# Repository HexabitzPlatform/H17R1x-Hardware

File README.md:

# H17R1x-Hardware
Hexabitz 10A(RMS)/85V Stepper Drive Module Hardware Design

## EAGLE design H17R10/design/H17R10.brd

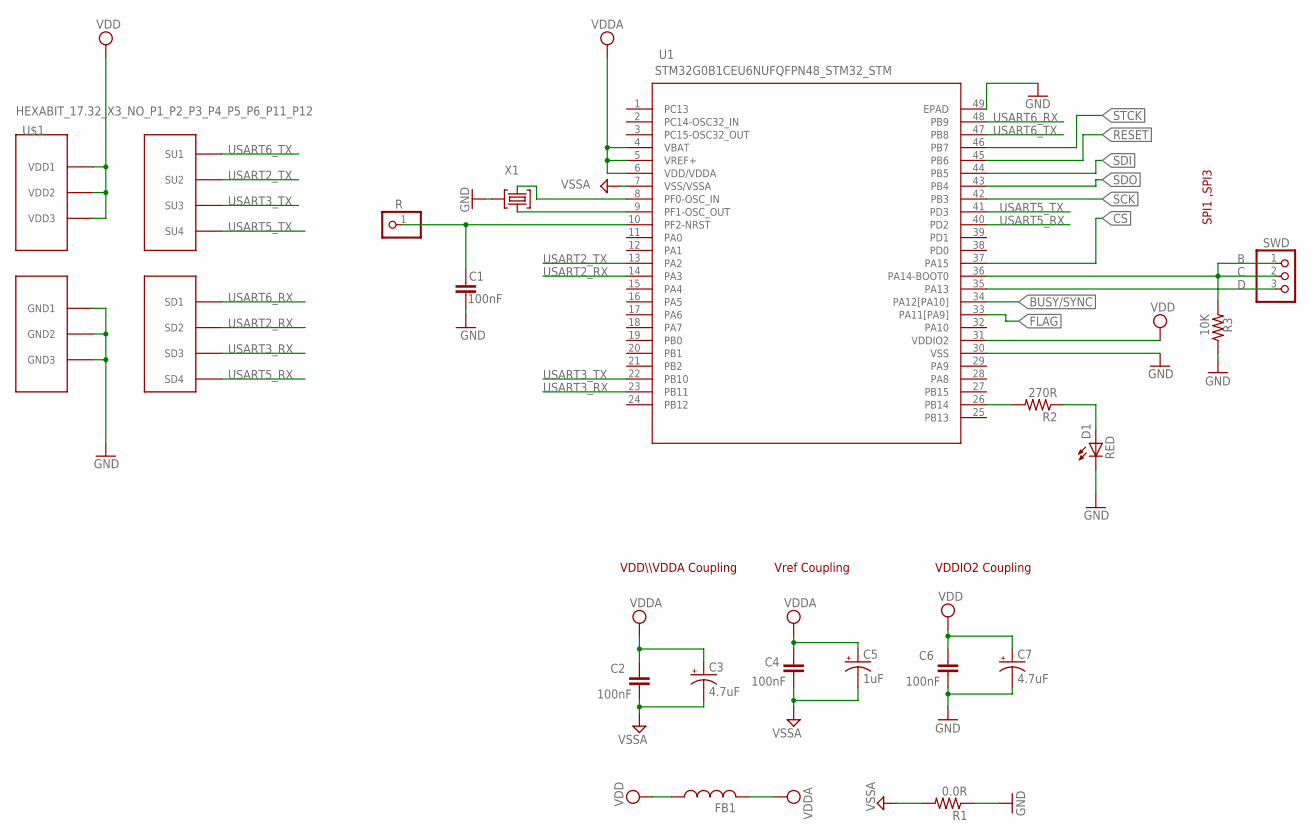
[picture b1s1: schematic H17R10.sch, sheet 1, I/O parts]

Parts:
C1: 100nF; C-0603; TOLERANCE 10%; VOLTAGE_RATING 16.0 V; MPN 0603YC104K4T2A
C2, C4, C6: 100nF; C-0603; TOLERANCE 10%; VOLTAGE_RATING 16.0 V; MPN '0603YC104K4T2A
C3: 4.7uF; C-0805-POL; TOLERANCE 20%; VOLTAGE_RATING 10.0 V; MPN '10TPU4R7MSI
C5: 1uF; C-0805-POL; TOLERANCE 20%; VOLTAGE_RATING 10.0 V; MPN 'CC0805KKX7R7BB105
C7: 4.7uF; C-0805-POL; TOLERANCE 10%; VOLTAGE_RATING 16.0 V; MPN '10TPU4R7MSI
D1: RED; VLMS1300-GS08
FB1: FB-TDK_MMZ1608Y300B; MPN MMZ1608Y300BTA00
R: PINHD-1X1; 1X01
R1: 0.0R; R-0603; MPN RC0603JR-070RL
R2: 270R; R-0603; MPN 'ERJ-3GEYJ271V
R3: 10K; R-0603; MPN '060300J0103T5E
SWD: PINHD-1X3; 1X03
U1: STM32G0B1CEU6NUFQFPN48_STM32_STM; HEXABITZ_ICS_UFQFPN48_STM32_STM
U$1: HEXABIT_17.32_X3_NO_P1_P2_P3_P4_P5_P6_P11_P12
X1: 8MHZ; XTALL_CSTCE8M00G52; MPN CSTNE8M00G550000R0

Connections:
BUSY/SYNC: U1.34 (PA12[PA10]); also elsewhere on the board
C: R3.2, SWD.1, SWD.2, U1.36 (PA14-BOOT0)
CS: U1.37 (PA15); also elsewhere on the board
D: SWD.3, U1.35 (PA13)
FLAG: U1.33 (PA11[PA9]); also elsewhere on the board
GND: C1.1, C6.1, C7.2 (-), D1.C, R1.1, R3.1, U1.30 (VSS), U1.49 (EPAD), U$1.PAD_PD12 (GND1), U$1.PAD_PD17 (GND2), U$1.PAD_PD19 (GND3), X1.P$2 (2)
unnamed: U1.8 (PF0-OSC_IN), X1.P$1 (1)
unnamed: U1.9 (PF1-OSC_OUT), X1.P$3 (3)
unnamed: C1.2, R.1, U1.10 (PF2-NRST)
unnamed: R2.2, U1.26 (PB14)
unnamed: D1.A, R2.1
RESET: U1.45 (PB6); also elsewhere on the board
SCK: U1.42 (PB3); also elsewhere on the board
SDI: U1.44 (PB5); also elsewhere on the board
SDO: U1.43 (PB4); also elsewhere on the board
STCK: U1.46 (PB7); also elsewhere on the board
USART2_RX: U1.14 (PA3), U$1.PAD_PD1 (SD2)
USART2_TX: U1.13 (PA2), U$1.PAD_PU1 (SU2)
USART3_RX: U1.23 (PB11), U$1.PAD_PD2 (SD3)
USART3_TX: U1.22 (PB10), U$1.PAD_PU2 (SU3)
USART5_RX: U1.40 (PD2), U$1.PAD_PD8 (SD4)
USART5_TX: U1.41 (PD3), U$1.PAD_PU8 (SU4)
USART6_RX: U1.48 (PB9), U$1.PAD_PD3 (SD1)
USART6_TX: U1.47 (PB8), U$1.PAD_PU3 (SU1)
VDD: C6.2, C7.1 (+), FB1.1, U1.31 (VDDIO2), U$1.PAD_PU12 (VDD1), U$1.PAD_PU17 (VDD2), U$1.PAD_PU19 (VDD3)
VDDA: C2.2, C3.1 (+), C4.2, C5.1 (+), FB1.2, U1.4 (VBAT), U1.5 (VREF+), U1.6 (VDD/VDDA); also elsewhere on the board
VSSA: C2.1, C3.2 (-), C4.1, C5.2 (-), R1.2, U1.7 (VSS/VSSA); also elsewhere on the board

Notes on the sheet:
VDDIO2 Coupling
VDD\\\VDDA Coupling
Vref Coupling
SPI1 ,SPI3

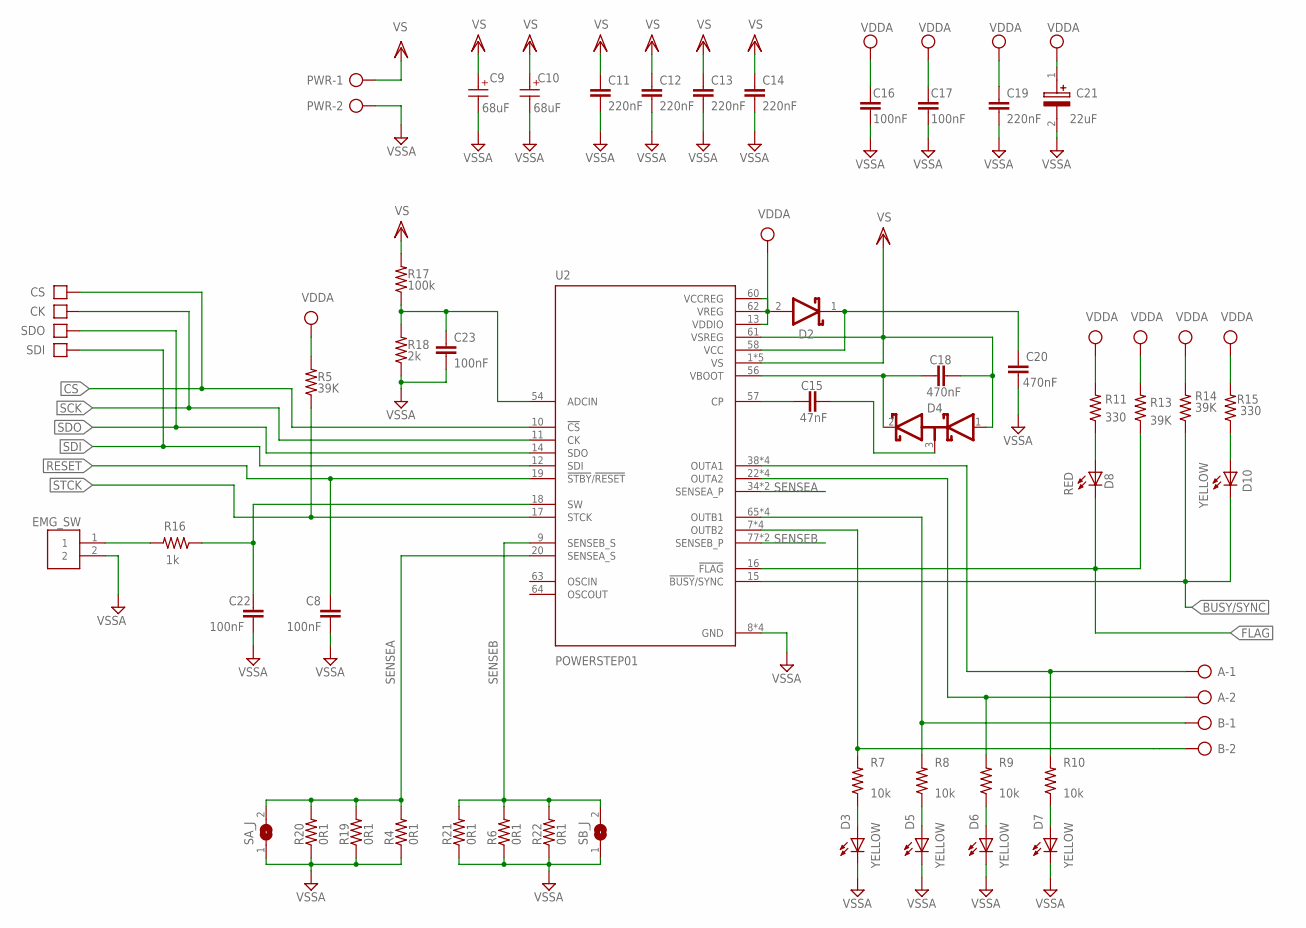
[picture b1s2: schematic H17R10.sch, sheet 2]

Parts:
A: AK500/2
B: AK500/2
C8, C22, C23: 100nF; C-0603; MPN C1608X7R1H104K080AA
C9, C10: 68uF; WCAP-ASLI_12.5X14(DXL)
C11, C12, C13, C14: 220nF; C-0805
C15: 47nF; C-0805; VOLTAGE_RATING 100V; MPN C0805C473K1RACTU
C16, C17: 100nF; C-0603; TOLERANCE 10%; VOLTAGE_RATING 16.0 V; MPN '0603YC104K4T2A
C18, C20: 470nF; C-0603; VOLTAGE_RATING 100V; MPN CGA3E3X7R1E474K080AE
C19: 220nF; C-0603; MPN CGA3E3X7R1V224K080AE
C21: 22uF; T491A
CK: PAD4
CS: PAD4
D2: STMICROELECTRONICS_BAT46ZFILMSTMICROELECTRONICS_B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; STMICROELECTRONICS_BAT46ZFILM_3
D3, D5, D6, D7, D10: YELLOW; VLMY1300-GS08; MPN LTST-C170YKT
D4: STMICROELECTRONICS_BAR43SFILMSTMICROELECTRONICS_B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; STMICROELECTRONICS_BAR43SFILM_0
D8: RED; VLMS1300-GS08; MPN LTST-C170-EKT
EMG_SW: 3-644456-2; TE_3-644456-2
PWR: AK500/2
R4, R6, R19, R20, R21, R22: 0R1; R2512; MPN PE2512FKE7W0R1L
R5, R13, R14: 39K; R-0603; MPN RC0603FR-0739KL
R7, R8, R9, R10: 10k; R-0805; MPN ERJ-6GEYJ103V
R11, R15: 330; R-0603; MPN RC0603JR-07330RL
R16: 1k; R-0603; MPN RC0603JR-07330RL
R17: 100k; R-0603; MPN RC0603FR-0739KL
R18: 2k; R-0603; MPN RC0603FR-0739KL
SA_J: SJW
SB_J: SJW
SDI: PAD4
SDO: PAD4
U2: POWERSTEP01; IC_POWERSTEP01

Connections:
BUSY/SYNC: D10.C, R14.1, U2.15 (!BUSY!/SYNC); also elsewhere on the board
CS: CS.P$1, U2.10 (!CS); also elsewhere on the board
FLAG: D8.C, R13.1, U2.16 (!FLAG); also elsewhere on the board
unnamed: C22.1, R16.1, U2.18 (SW)
unnamed: C15.1, U2.57 (CP)
unnamed: D10.A, R15.1
unnamed: D7.A, R10.1
unnamed: C23.1, R17.1, R18.2, U2.54 (ADCIN)
unnamed: D3.A, R7.1
unnamed: D8.A, R11.1
unnamed: D5.A, R8.1
unnamed: D6.A, R9.1
unnamed: C18.2, D4.2 (K1), U2.56 (VBOOT)
unnamed: C20.1, D2.1 (CATHODE), U2.58 (VCC)
unnamed: C15.2, D4.3 (A1/K2)
OUTA1: A.2, R10.2, U2.38 (OUTA1), U2.42 (OUTA1), U2.53 (OUTA1), U2.EPAD4 (OUTA1)
OUTA2: A.1, R9.2, U2.22 (OUTA2), U2.33 (OUTA2), U2.37 (OUTA2), U2.EPAD3 (OUTA2)
OUTB1: B.1, R8.2, U2.65 (OUTB1), U2.76 (OUTB1), U2.80 (OUTB1), U2.EPAD7 (OUTB1)
OUTB2: B.2, R7.2, U2.7 (OUTB2), U2.81 (OUTB2), U2.85 (OUTB2), U2.EPAD8 (OUTB2)
RESET: C8.1, U2.19 (!STBY!/!RESET); also elsewhere on the board
SCK: CK.P$1, U2.11 (CK); also elsewhere on the board
SDI: SDI.P$1, U2.12 (SDI); also elsewhere on the board
SDO: SDO.P$1, U2.14 (SDO); also elsewhere on the board
SENSEA: R4.2, R19.2, R20.2, SA_J.2, U2.20 (SENSEA_S), U2.34 (SENSEA_P), U2.39 (SENSEA_P)
SENSEB: R6.2, R21.2, R22.2, SB_J.2, U2.9 (SENSEB_S), U2.77 (SENSEB_P), U2.82 (SENSEB_P)
STCK: R5.1, U2.17 (STCK); also elsewhere on the board
SW: EMG_SW.1, R16.2
VDDA: C16.2, C17.2, C19.1, C21.1 (+), D2.2 (ANODE), R5.2, R11.2, R13.2, R14.2, R15.2, U2.13 (VDDIO), U2.60 (VCCREG), U2.62 (VREG); also elsewhere on the board
VS: C9.1 (+), C10.1 (+), C11.1, C12.1, C13.1, C14.1, C18.1, D4.1 (A2), PWR.1, R17.2, U2.1 (VS), U2.23 (VS), U2.43 (VS), U2.55 (VS), U2.61 (VSREG), U2.66 (VS)
VSSA: C8.2, C9.2 (-), C10.2 (-), C11.2, C12.2, C13.2, C14.2, C16.1, C17.1, C19.2, C20.2, C21.2 (-), C22.2, C23.2, D3.C, D5.C, D6.C, D7.C, EMG_SW.2, PWR.2, R4.1, R6.1, R18.1, R19.1, R20.1, R21.1, R22.1, SA_J.1, SB_J.1, U2.8 (GND), U2.21 (GND), U2.59 (GND), U2.EPAD9 (GND); also elsewhere on the board

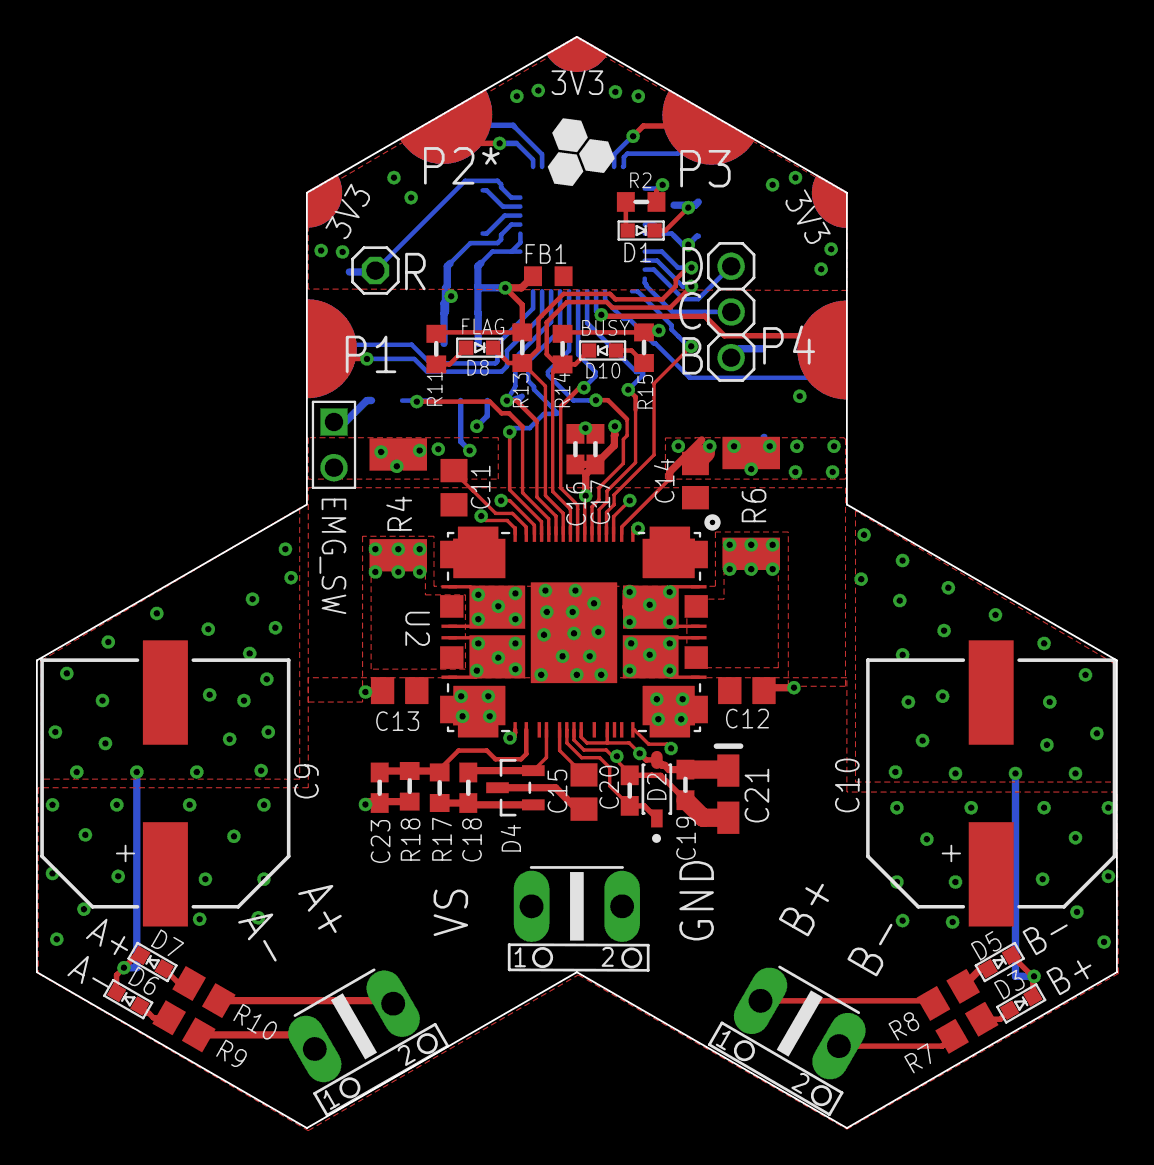
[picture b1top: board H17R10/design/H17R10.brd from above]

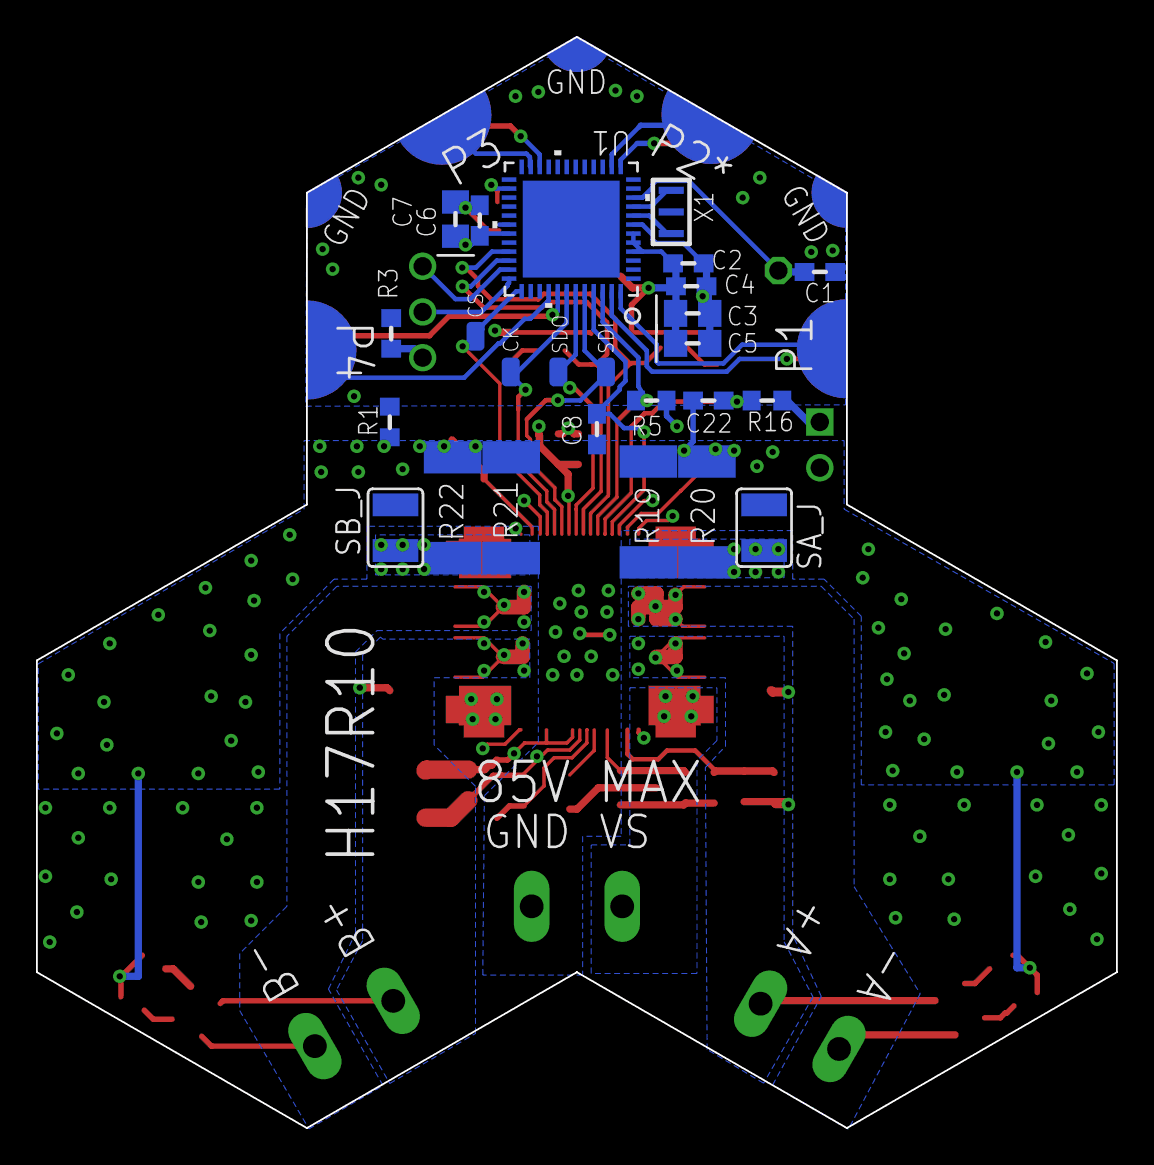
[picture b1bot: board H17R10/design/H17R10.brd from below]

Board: 4 copper layers, 60.0 x 60.6 mm, 70 parts (25 on the bottom side), 47 nets.

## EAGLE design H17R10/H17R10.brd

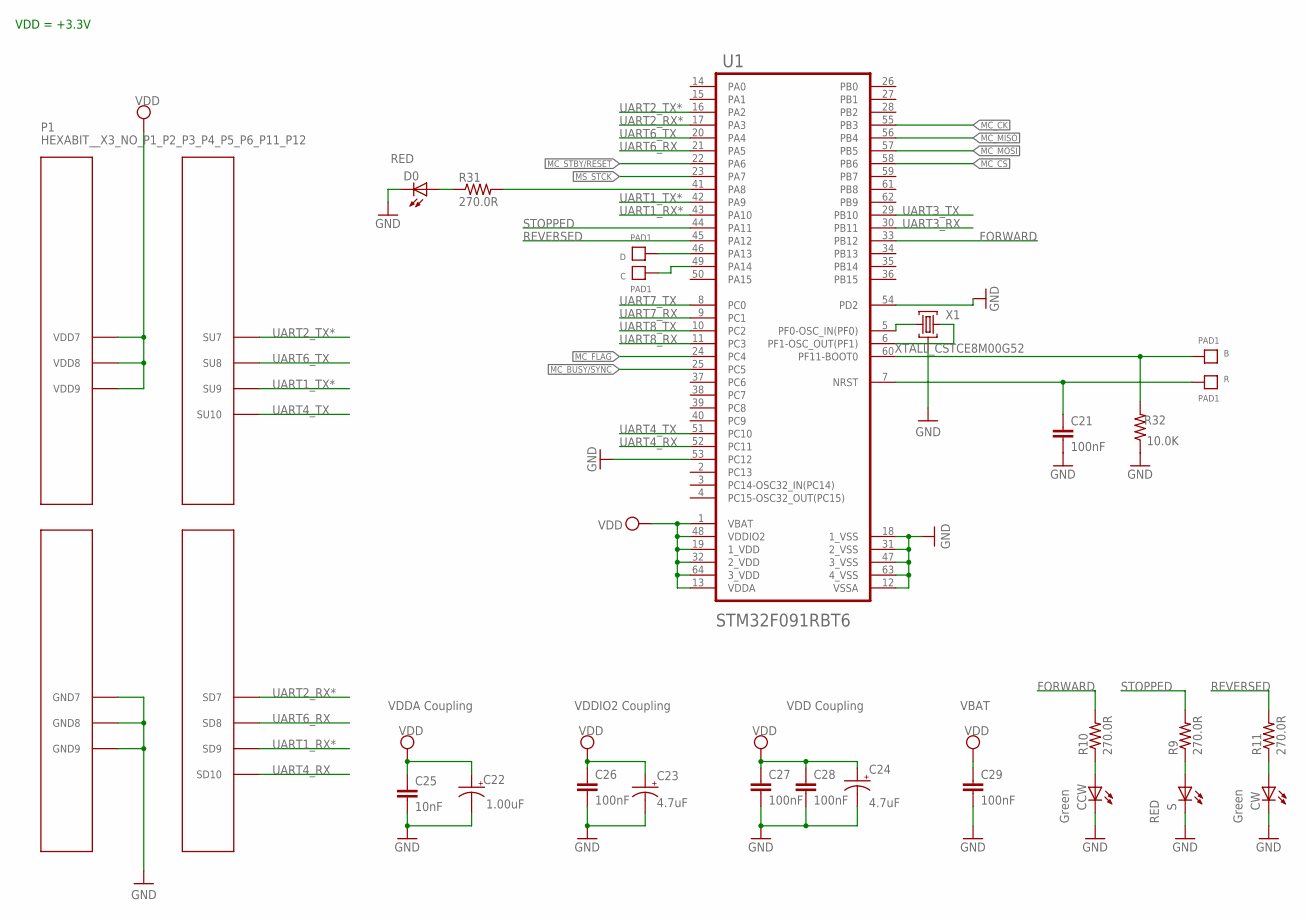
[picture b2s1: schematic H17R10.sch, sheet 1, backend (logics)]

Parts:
B: PAD1
C: PAD1
C21, C26, C28: 100nF; C-0603; TOLERANCE 10%; VOLTAGE_RATING 10V; MPN C0603C104K8RACTU
C22: 1.00uF; C-0805-POL; TOLERANCE 10%; VOLTAGE_RATING 16V; MPN CC0805KKX7R7BB105
C23, C24: 4.7uF; C-0805-POL; TOLERANCE 10%; VOLTAGE_RATING 25V; MPN GRM21BC81E475KA12L
C25: 10nF; C-0603; TOLERANCE 10%; VOLTAGE_RATING 50V; MPN C0603C103K5RACTU
C27: 100nF; C-0603; TOLERANCE 10%; VOLTAGE_RATING 10; MPN C0603C104K8RACTU
C29: 100nF; C-0603; TOLERANCE 10V; VOLTAGE_RATING 10%; MPN C0603C104K8RACTU
CCW: Green; VLMTG1300-GS08; MPN VLMS1300-GS08
CW: Green; VLMTG1300-GS08; MPN VLMS1300-GS08
D: PAD1
D0: RED; VLMS1300-GS08; MPN VLMS1300-GS08
P1: HEXABIT__X3_NO_P1_P2_P3_P4_P5_P6_P11_P12; HEXABIT_17.32_X3_NO_P1_P2_P3_P4_P5_P6_P11_P12
R: PAD1
R9, R10, R11, R31: 270.0R; R-0603; TOLERANCE 1%; MPN RC0603FR-07270RL
R32: 10.0K; R-0603; TOLERANCE 5%; MPN RC0603JR-0710KL
S: RED; VLMS1300-GS08; MPN VLMS1300-GS08
U1: STM32F091RBT6STMICROELECTRONICS_STM32F091RBT6_0_1; STMICROELECTRONICS_STM32F091RBT6_1
X1: XTALL_CSTCE8M00G52

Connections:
B1: B.P$1, B.P$2, R32.2, U1.60 (PF11-BOOT0)
FORWARD: R10.2, U1.33 (PB12)
GND: C21.2, C22.2 (-), C23.2 (-), C24.2 (-), C25.2, C26.2, C27.2, C28.2, C29.2, CCW.C, CW.C, D0.C, P1.PAD_PD12 (GND7), P1.PAD_PD17 (GND8), P1.PAD_PD19 (GND9), R32.1, S.C, U1.12 (VSSA), U1.18 (1_VSS), U1.31 (2_VSS), U1.47 (3_VSS), U1.53 (PC12), U1.54 (PD2), U1.63 (4_VSS), X1.P$2 (2); also elsewhere on the board
MC_BUSY/SYNC: U1.25 (PC5); also elsewhere on the board
MC_CK: U1.55 (PB3); also elsewhere on the board
MC_CS: U1.58 (PB6); also elsewhere on the board
MC_FLAG: U1.24 (PC4); also elsewhere on the board
MC_MISO: U1.56 (PB4); also elsewhere on the board
MC_MOSI: U1.57 (PB5); also elsewhere on the board
MC_STBY/RESET: U1.22 (PA6); also elsewhere on the board
MS_STCK: U1.23 (PA7); also elsewhere on the board
unnamed: R31.2, U1.41 (PA8)
unnamed: D0.A, R31.1
unnamed: U1.5 (PF0-OSC_IN(PF0)), X1.P$1 (1)
unnamed: U1.6 (PF1-OSC_OUT(PF1)), X1.P$3 (3)
unnamed: D.P$1, D.P$2, U1.46 (PA13)
unnamed: C.P$1, C.P$2, U1.49 (PA14)
unnamed: R9.1, S.A
unnamed: CCW.A, R10.1
unnamed: CW.A, R11.1
R1: C21.1, R.P$1, R.P$2, U1.7 (NRST)
REVERSED: R11.2, U1.45 (PA12)
STOPPED: R9.2, U1.44 (PA11)
UART1_RX*: P1.PAD_PD2 (SD9), U1.43 (PA10)
UART1_TX*: P1.PAD_PU2 (SU9), U1.42 (PA9)
UART2_RX*: P1.PAD_PD3 (SD7), U1.17 (PA3)
UART2_TX*: P1.PAD_PU3 (SU7), U1.16 (PA2)
UART3_RX: U1.30 (PB11)
UART3_TX: U1.29 (PB10)
UART4_RX: P1.PAD_PD8 (SD10), U1.52 (PC11)
UART4_TX: P1.PAD_PU8 (SU10), U1.51 (PC10)
UART6_RX: P1.PAD_PD1 (SD8), U1.21 (PA5)
UART6_TX: P1.PAD_PU1 (SU8), U1.20 (PA4)
UART7_RX: U1.9 (PC1)
UART7_TX: U1.8 (PC0)
UART8_RX: U1.11 (PC3)
UART8_TX: U1.10 (PC2)
VDD: C22.1 (+), C23.1 (+), C24.1 (+), C25.1, C26.1, C27.1, C28.1, C29.1, P1.PAD_PU12 (VDD7), P1.PAD_PU17 (VDD8), P1.PAD_PU19 (VDD9), U1.1 (VBAT), U1.13 (VDDA), U1.19 (1_VDD), U1.32 (2_VDD), U1.48 (VDDIO2), U1.64 (3_VDD); also elsewhere on the board

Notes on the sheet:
VDDA Coupling
VDDIO2 Coupling
VDD Coupling
VBAT
VDD = +3.3V

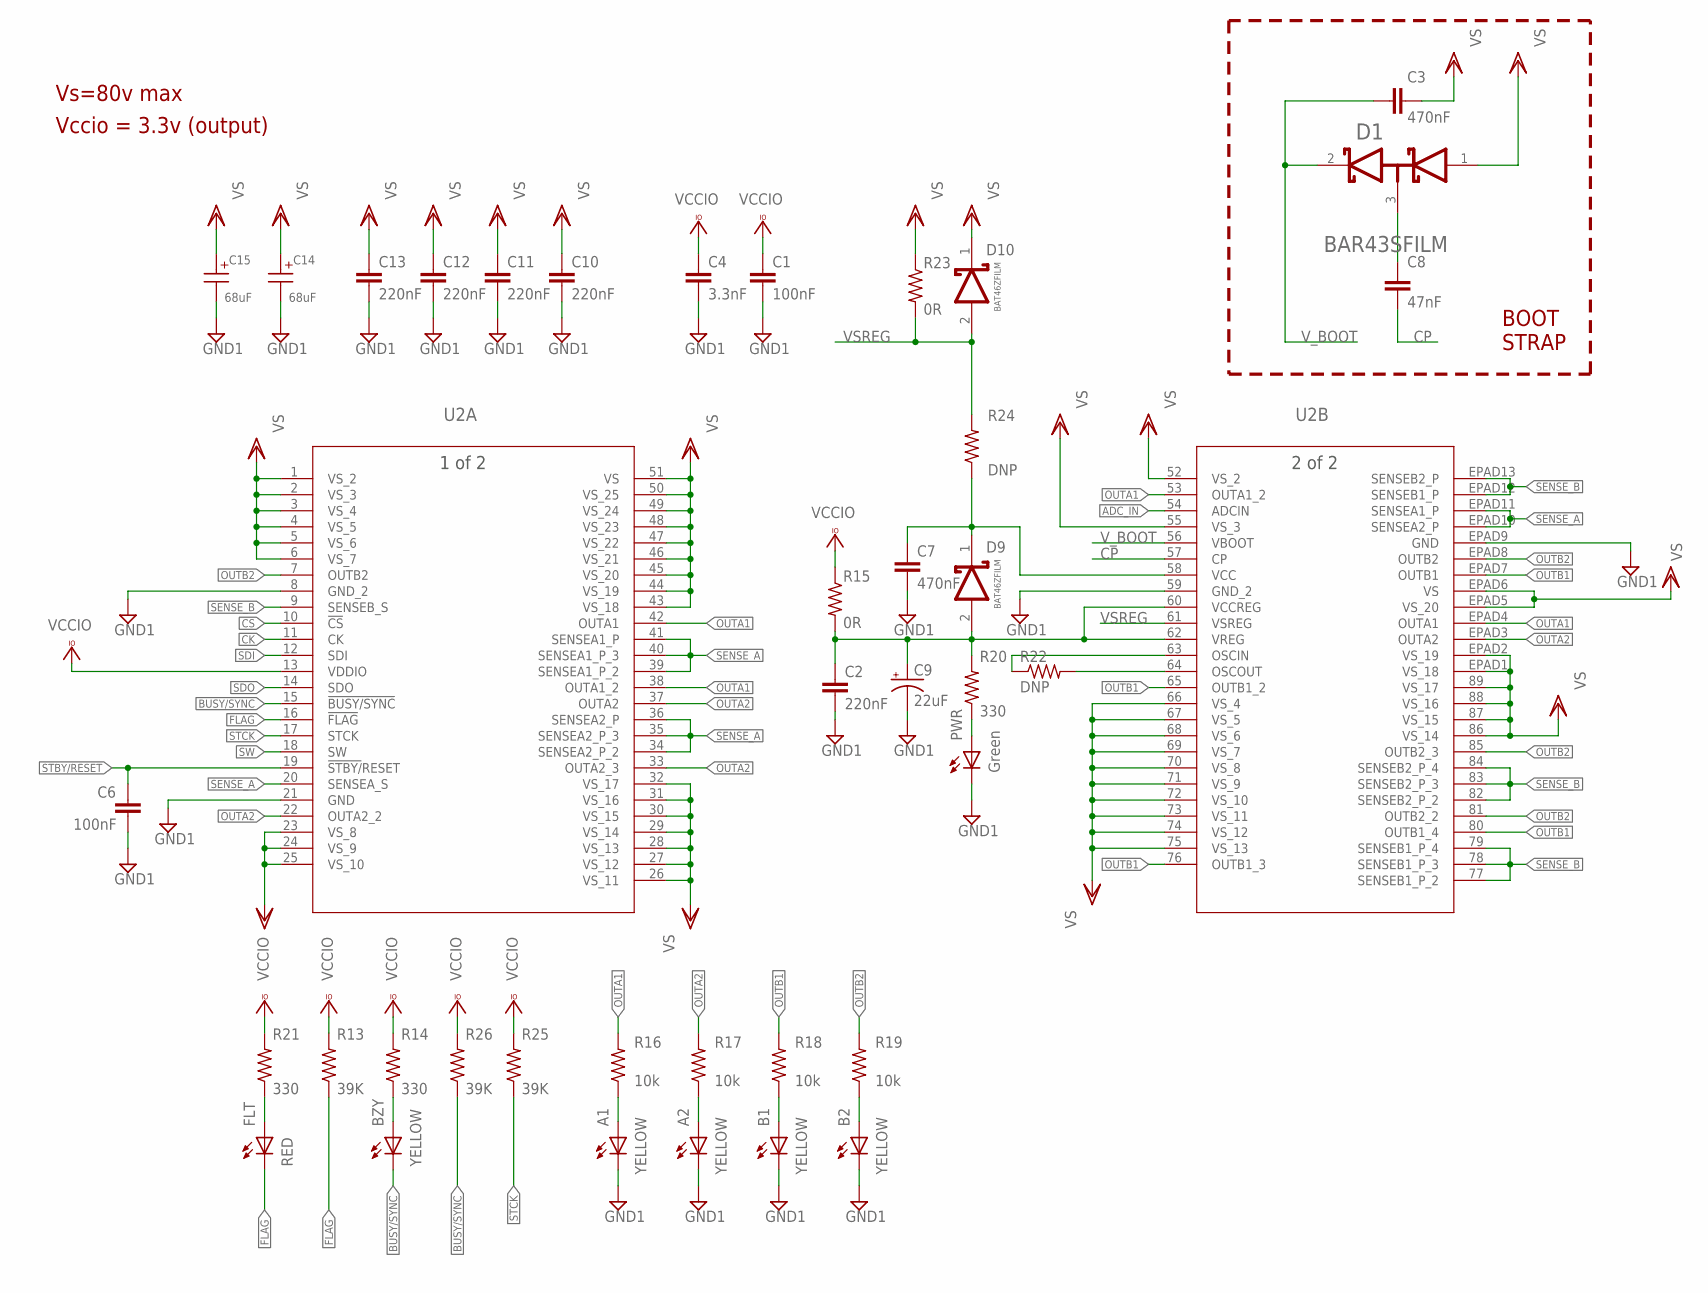
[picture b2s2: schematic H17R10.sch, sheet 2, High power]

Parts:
A1, A2: YELLOW; VLMY1300-GS08; MPN LTST-C170YKT
B1, B2: YELLOW; VLMY1300-GS08; MPN LTST-C170YKT
BZY: YELLOW; VLMY1300-GS08; MPN LTST-C170YKT
C1, C6: 100nF; C-0603; MPN C1608X7R1H104K080AA
C2: 220nF; C-0603; MPN CGA3E3X7R1V224K080AE
C3, C7: 470nF; C-0603; MPN CGA3E3X7R1E474K080AE
C4: 3.3nF; C-0603; MPN C1608X7R1H104K080AA
C8: 47nF; C-0805; VOLTAGE_RATING 100V; MPN C0805C473K1RACTU
C9: 22uF; C-0805-POL; VOLTAGE_RATING 6.3V; MPN T491A226K006AT
C10, C11, C12, C13: 220nF; C-0805
C14, C15: 68uF; WCAP-ASLI_12.5X14(DXL)
D1: STMICROELECTRONICS_BAR43SFILMSTMICROELECTRONICS_B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; STMICROELECTRONICS_BAR43SFILM_0
D9, D10: STMICROELECTRONICS_BAT46ZFILMSTMICROELECTRONICS_B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; STMICROELECTRONICS_BAT46ZFILM_3
FLT: RED; VLMS1300-GS08; MPN LTST-C170-EKT
PWR: Green; VLMTG1300-GS08; MPN LTST-C170GKT
R13, R25, R26: 39K; R-0603; MPN RC0603FR-0739KL
R14, R20, R21: 330; R-0603; MPN RC0603JR-07330RL
R15, R23: 0R; R-0603; MPN RC0603JR-070RL
R16, R17, R18, R19: 10k; R-0805; MPN ERJ-6GEYJ103V
R22: DNP; R-0603; MPN DNP
R24: DNP; R-0805
U2: POWERSTEP01; VFQFPN89_11X14X1_STM

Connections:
ADC_IN: U2.54 (ADCIN); also elsewhere on the board
BUSY/SYNC: BZY.C, R26.1, U2.15 (!BUSY/SYNC); also elsewhere on the board
CK: U2.11 (CK); also elsewhere on the board
CP: C8.1, U2.57 (CP)
CS: U2.10 (!CS); also elsewhere on the board
FLAG: FLT.C, R13.1, U2.16 (!FLAG); also elsewhere on the board
GND1: A1.C, A2.C, B1.C, B2.C, C1.2, C2.2, C4.2, C6.2, C7.2, C9.2 (-), C10.2, C11.2, C12.2, C13.2, C14.2 (-), C15.2 (-), PWR.C, U2.8 (GND_2), U2.21 (GND), U2.59 (GND_2), U2.EPAD9 (GND); also elsewhere on the board
unnamed: C2.1, C9.1 (+), D9.2 (ANODE), R15.2, R20.2, U2.60 (VCCREG), U2.62 (VREG)
unnamed: C8.2, D1.3 (A1/K2)
unnamed: C7.1, D9.1 (CATHODE), R24.1, U2.58 (VCC)
unnamed: A1.A, R16.1
unnamed: BZY.A, R14.1
unnamed: FLT.A, R21.1
unnamed: PWR.A, R20.1
unnamed: A2.A, R17.1
unnamed: B1.A, R18.1
unnamed: B2.A, R19.1
unnamed: R22.2, U2.64 (OSCOUT)
unnamed: R22.1, U2.63 (OSCIN)
OUTA1: R16.2, U2.38 (OUTA1_2), U2.42 (OUTA1), U2.53 (OUTA1_2), U2.EPAD4 (OUTA1); also elsewhere on the board
OUTA2: R17.2, U2.22 (OUTA2_2), U2.33 (OUTA2_3), U2.37 (OUTA2), U2.EPAD3 (OUTA2); also elsewhere on the board
OUTB1: R18.2, U2.65 (OUTB1_2), U2.76 (OUTB1_3), U2.80 (OUTB1_4), U2.EPAD7 (OUTB1); also elsewhere on the board
OUTB2: R19.2, U2.7 (OUTB2), U2.81 (OUTB2_2), U2.85 (OUTB2_3), U2.EPAD8 (OUTB2); also elsewhere on the board
SDI: U2.12 (SDI); also elsewhere on the board
SDO: U2.14 (SDO); also elsewhere on the board
SENSE_A: U2.20 (SENSEA_S), U2.34 (SENSEA2_P_2), U2.35 (SENSEA2_P_3), U2.36 (SENSEA2_P), U2.39 (SENSEA1_P_2), U2.40 (SENSEA1_P_3), U2.41 (SENSEA1_P), U2.EPAD10 (SENSEA2_P), U2.EPAD11 (SENSEA1_P); also elsewhere on the board
SENSE_B: U2.9 (SENSEB_S), U2.77 (SENSEB1_P_2), U2.78 (SENSEB1_P_3), U2.79 (SENSEB1_P_4), U2.82 (SENSEB2_P_2), U2.83 (SENSEB2_P_3), U2.84 (SENSEB2_P_4), U2.EPAD12 (SENSEB1_P), U2.EPAD13 (SENSEB2_P); also elsewhere on the board
STBY/RESET: C6.1, U2.19 (!STBY/!RESET); also elsewhere on the board
STCK: R25.1, U2.17 (STCK); also elsewhere on the board
SW: U2.18 (SW); also elsewhere on the board
VCCIO: C1.1, C4.1, R13.2, R14.2, R15.1, R21.2, R25.2, R26.2, U2.13 (VDDIO); also elsewhere on the board
VSREG: D10.2 (ANODE), R23.2, R24.2, U2.61 (VSREG)
VSS: C3.2, C10.1, C11.1, C12.1, C13.1, C14.1 (+), C15.1 (+), D1.1 (A2), D10.1 (CATHODE), R23.1, U2.1 (VS_2), U2.2 (VS_3), U2.3 (VS_4), U2.4 (VS_5), U2.5 (VS_6), U2.6 (VS_7), U2.23 (VS_8), U2.24 (VS_9), U2.25 (VS_10), U2.26 (VS_11), U2.27 (VS_12), U2.28 (VS_13), U2.29 (VS_14), U2.30 (VS_15), U2.31 (VS_16), U2.32 (VS_17), U2.43 (VS_18), U2.44 (VS_19), U2.45 (VS_20), U2.46 (VS_21), U2.47 (VS_22), U2.48 (VS_23), U2.49 (VS_24), U2.50 (VS_25), U2.51 (VS), U2.52 (VS_2), U2.55 (VS_3), U2.66 (VS_4), U2.67 (VS_5), U2.68 (VS_6), U2.69 (VS_7), U2.70 (VS_8), U2.71 (VS_9), U2.72 (VS_10), U2.73 (VS_11), U2.74 (VS_12), U2.75 (VS_13), U2.86 (VS_14), U2.87 (VS_15), U2.88 (VS_16), U2.89 (VS_17), U2.EPAD1 (VS_18), U2.EPAD2 (VS_19), U2.EPAD5 (VS_20), U2.EPAD6 (VS); also elsewhere on the board
V_BOOT: C3.1, D1.2 (K1), U2.56 (VBOOT)

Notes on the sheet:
BOOT STRAP
Vs=80v max
Vccio = 3.3v (output)

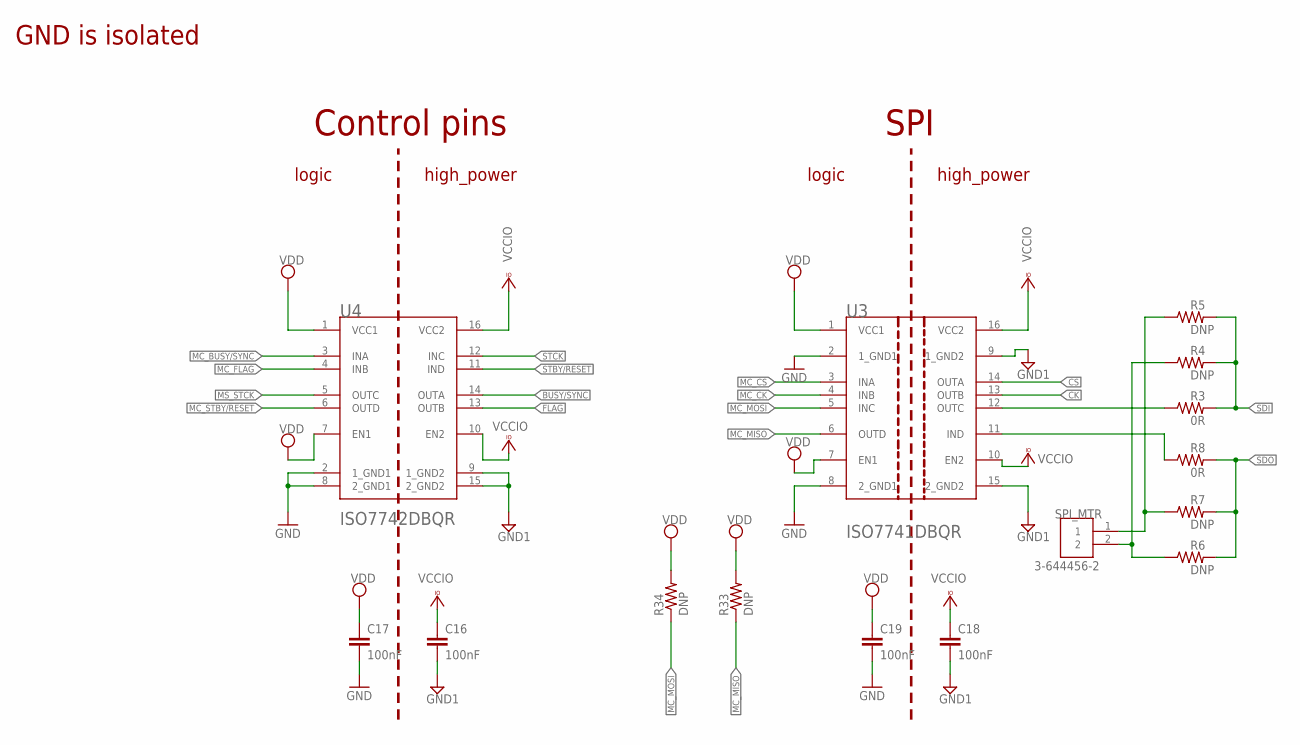
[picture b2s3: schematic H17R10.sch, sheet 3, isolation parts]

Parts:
C16, C17, C18, C19: 100nF; C-0603; MPN C1608X7R1H104K080AA
R3, R8: 0R; R-0603; MPN RC0603JR-070RL
R4, R5, R6, R7: DNP; R-0603; MPN DNP
R33, R34: DNP; R-0603
SPI_MTR: 3-644456-2; TE_3-644456-2
U3: TEXAS_INSTRUMENTS_ISO7741DBQRTEXAS_INSTRUMENTS_IS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; TEXAS_INSTRUMENTS_ISO7741DBQR_0
U4: TEXAS_INSTRUMENTS_ISO7742DBQRTEXAS_INSTRUMENTS_IS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; TEXAS_INSTRUMENTS_ISO7742DBQR_3

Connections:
BUSY/SYNC: U4.14 (OUTA); also elsewhere on the board
CK: U3.13 (OUTB); also elsewhere on the board
CS: U3.14 (OUTA); also elsewhere on the board
FLAG: U4.13 (OUTB); also elsewhere on the board
GND: C17.2, C19.2, U3.2 (1_GND1), U3.8 (2_GND1), U4.2 (1_GND1), U4.8 (2_GND1); also elsewhere on the board
GND1: C16.2, C18.2, U3.9 (1_GND2), U3.15 (2_GND2), U4.9 (1_GND2), U4.15 (2_GND2); also elsewhere on the board
MC_BUSY/SYNC: U4.3 (INA); also elsewhere on the board
MC_CK: U3.4 (INB); also elsewhere on the board
MC_CS: U3.3 (INA); also elsewhere on the board
MC_FLAG: U4.4 (INB); also elsewhere on the board
MC_MISO: R33.1, U3.6 (OUTD); also elsewhere on the board
MC_MOSI: R34.1, U3.5 (INC); also elsewhere on the board
MC_STBY/RESET: U4.6 (OUTD); also elsewhere on the board
MS_STCK: U4.5 (OUTC); also elsewhere on the board
unnamed: R3.1, U3.12 (OUTC)
unnamed: R8.1, U3.11 (IND)
unnamed: R4.1, R6.1, SPI_MTR.2
unnamed: R5.1, R7.1, SPI_MTR.1
SDI: R3.2, R4.2, R5.2; also elsewhere on the board
SDO: R6.2, R7.2, R8.2; also elsewhere on the board
STBY/RESET: U4.11 (IND); also elsewhere on the board
STCK: U4.12 (INC); also elsewhere on the board
VCCIO: C16.1, C18.1, U3.10 (EN2), U3.16 (VCC2), U4.10 (EN2), U4.16 (VCC2); also elsewhere on the board
VDD: C17.1, C19.1, R33.2, R34.2, U3.1 (VCC1), U3.7 (EN1), U4.1 (VCC1), U4.7 (EN1); also elsewhere on the board

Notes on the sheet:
GND is isolated
high_power
logic
SPI
Control pins

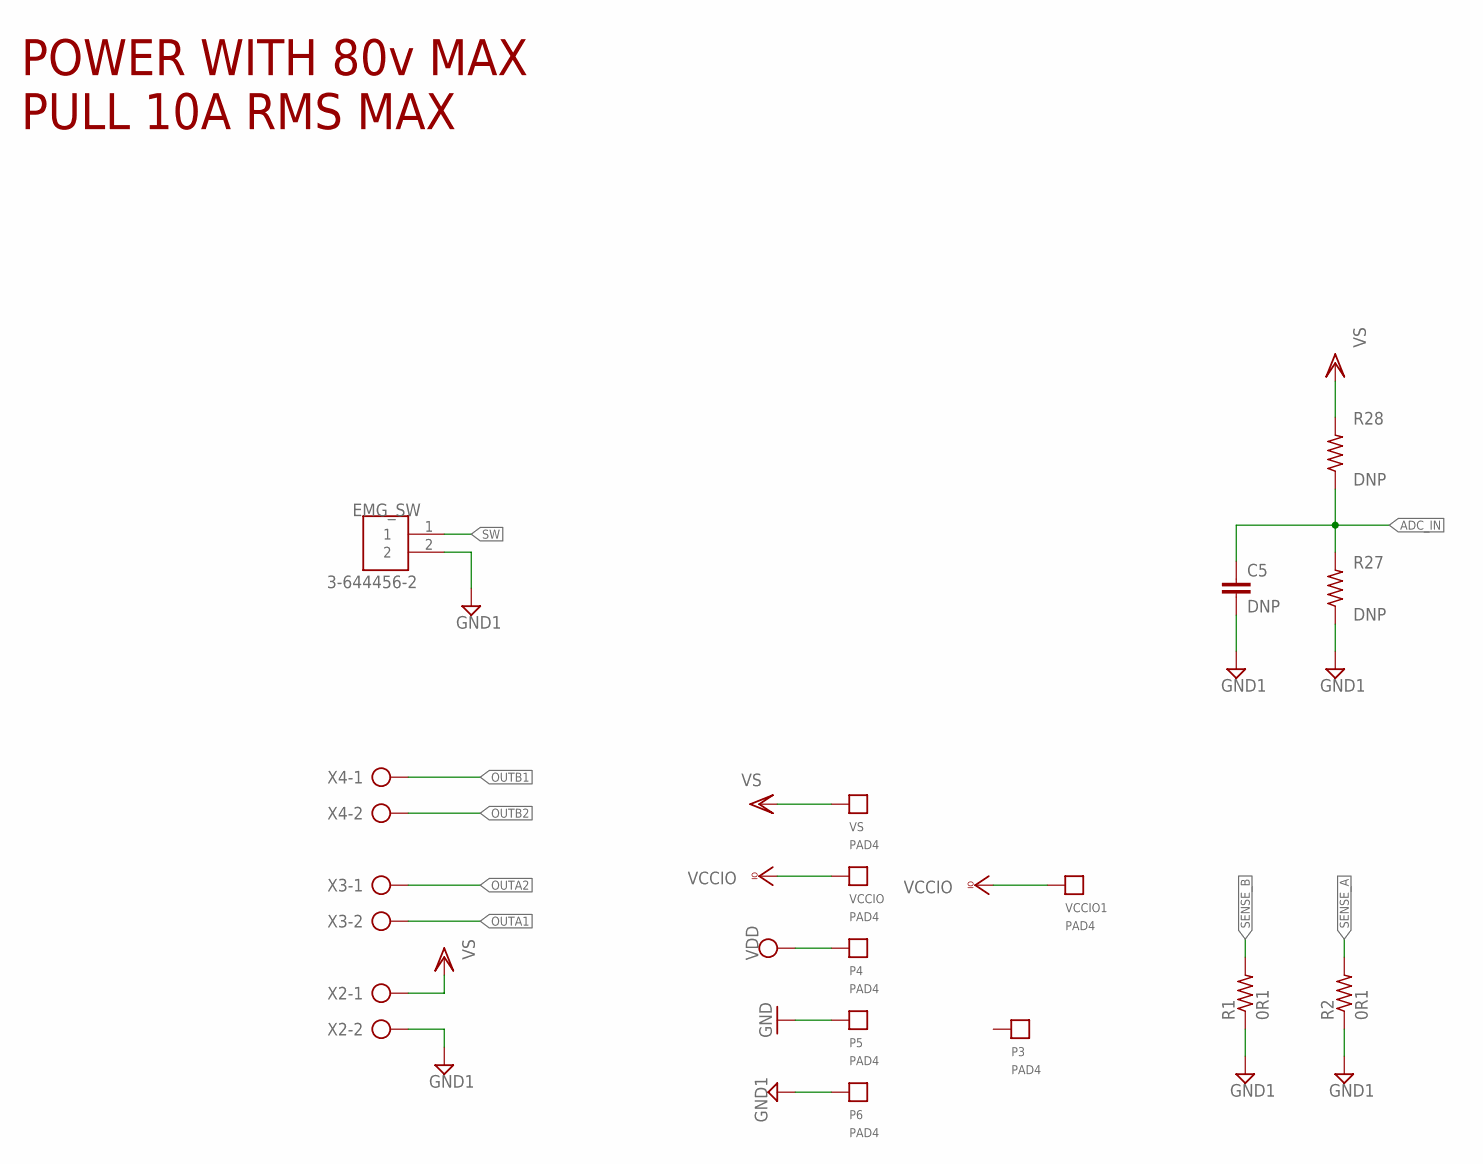
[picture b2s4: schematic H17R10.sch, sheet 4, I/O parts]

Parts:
C5: DNP; C-0603
EMG_SW: 3-644456-2; TE_3-644456-2
P3, P4, P5, P6: PAD4
R1, R2: 0R1; R2512; MPN PE2512FKE7W0R1L
R27: DNP; R-0603
R28: DNP; R-0805
VCCIO, VCCIO1: PAD4
VS: PAD4
X2, X3, X4: AK500/2

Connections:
ADC_IN: C5.1, R27.2, R28.1; also elsewhere on the board
GND: P5.P$1; also elsewhere on the board
GND1: C5.2, EMG_SW.2, P6.P$1, R1.1, R2.1, R27.1, X2.2; also elsewhere on the board
OUTA1: X3.2; also elsewhere on the board
OUTA2: X3.1; also elsewhere on the board
OUTB1: X4.1; also elsewhere on the board
OUTB2: X4.2; also elsewhere on the board
SENSE_A: R2.2; also elsewhere on the board
SENSE_B: R1.2; also elsewhere on the board
SW: EMG_SW.1; also elsewhere on the board
VCCIO: VCCIO.P$1, VCCIO1.P$1; also elsewhere on the board
VDD: P4.P$1; also elsewhere on the board
VSS: R28.2, VS.P$1, X2.1; also elsewhere on the board

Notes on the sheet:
POWER WITH 80v MAX PULL 10A RMS MAX

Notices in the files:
parts and their libraries:
COPYRIGHT: Copyright (C) 2018 Accelerated Designs. All rights reserved
COPYRIGHT: Copyright (C) 2022 Ultra Librarian. All rights reserved.
